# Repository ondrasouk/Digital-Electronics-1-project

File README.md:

# Týmový projekt do předmětu BPC-DE1 
# Název projektu: Konzole pro rotoped 

### Členové týmu

1. [Smejkal Marek](https://github.com/xsmejk30/Digital-electronics-1)
2. [Socha Jakub](https://github.com/xsocha00/Digital-electronics-1)
3. [Soukeník Ondřej](https://github.com/ondrasouk/Digital-electronics-1)
4. [Stupka Tomáš](https://github.com/ondrasouk/Digital-electronics-1)
5. [Šomšák Martin ](https://github.com/MartinSomsak00/DE1)

[Link to GitHub project folder](https://github.com/ondrasouk/Digital-Electronics-1-project)

## Úvod

Úkolem tohoto projektu bylo vytvořit konzoli pro měření otáček rotopedu. Toto měření následně vede na rozšíření jako napříkad měření rychlosti, ujeté vzdálenosti, průměrné rychlosti atd. 

V našem případě jsme se rozhodli pro snímání otáček použít čidlo [44E](https://dratek.cz/arduino/7735-halluv-senzor-44e.html?gclid=CjwKCAjwj6SEBhAOEiwAvFRuKIS_8uQ_ZEzr9x-yYRR3fPEQ0RS04KZdMaqaGm8xElUVrgnHnGZ3SxoCdZ4QAvD_BwE), který obsahuje halovu sondu. Napájecí napětí čidla je 4,5-24V Výstupem čidla je buď logická 0 nebo 1. Pokud tento sensor umístíme na pevný bod v blízkoti otáčenícího kola, je nutné přidat na otáčejí se kole magnetický puk. Následně při otáčení kola snímač vygeneruje signál pomocí kterého můžeme určit požadované veličiny.

Pro následní zobrazení měřené veličiny byl využit 4x7 segmentový displej a tři ledky pro indikaci zobrazovaného výstupu (zapnuto/vypnuto, přepínání zobrazení, reset systému).

## Popis zapojení 
Zapojení a PCB jsou navrženy v programu Eagle. 
V zapojení jsou použity 7 segmentové displeje se společnou anodou. Stejné segmenty jednotlivých digitů jsou pospojovány. Pmod JC slouží k přepínání napájení mezi jednotlivými digity. K Pmod JB jsou připojeny jednotlivé skupiny segmentů a k Pmod JA jsou připojeny LED a hallův senzor. Výhodnější by bylo pouřít jednou součástku obsahující 4 digity (stejně jako na desce Nexys A7), ale Eagle takovou součástku neobsahuje.
PADy 1, 2 a 3 slouží k připojení hallova senzoru. PAD1 je určen k připojení +5V protože použitý hallův senzor pracuje od 4,5V, ale na Pmod porty mají 3,3V. 

| **PCB** | **Pmod JA** | **Port** |
| :-: | :-: | :-: |
| AN0 | 4 | D12 |
| AN1 | 3 | A11 | 
| AN2 | 2 | B11 | 
| AN3 | 1 | G13 | 

| **PCB** | **Pmod JB** | **Port** |
| :-: | :-: | :-: |
| a | 1 | E15 |
| b | 2 | E16 | 
| c | 3 | D15 | 
| d | 4 | C15 | 
| e | 7 | J17 | 
| f | 8 | J18 | 
| g | 9 | K15 | 
| P | 10 | J15 |
| GND | 5 |  |
| 3,3V | 6 |  |

| **PCB** | **Pmod JC** | **Port** |
| :-: | :-: | :-: |
| LED1 | 1 | U12 |
| LED2 | 2 | V12 | 
| LED3 | 3 | V10 | 
| LED4 | 4 | V11 | 
| LED5 | 7 | T13 | 
| hall sensor | 8 | U13 | 

## Programová část
### Popis řešení měření času
Čidlo vždy vygeneruje klesající hranu, když kolem něj projede magnet umístěný na kole setrvačníku. V top modulu vstup invertujeme, pro snažší pochopení. Tento signál značí jednu otáčku setrvačníku, který simuluje setrvačnost jízdního kola a člověka na něm. Interval mezi klesajícími hranami je tedy doba za kterou virtuální kolo urazí jednu otočku kola. Podle vzorečku v=s/t můžeme vypočítat rychlost, kde s je virtuální vzdálenost jedné otočky setrvačníku (je tedy konstantní) a t je čas mezi signálem ze senzoru.

K měření času se dá použít hodinový zdroj z FPGA který má 100&nbsp;MHz. Rozlišovací schopnost 10&nbsp;ns je pro toto použití moc přesná a plítvali bychom zbytečně prostředky na např. 32 bitovém čitači, když můžeme použít 16 bitový. Tedy aby pro čas kolem 250&nbsp;us se musí prodloužit interval mezi náběžnými hranami. Pro tento účel byla použita dělička časových hodin v podobě modulu clock_enable, který byl využit z cvičení v předmětu DE1. Poté něčím musíme počítat jednotlivé pulzy. Zde byl využit naprogramovaný obousměrný čítač  ze cvičení, který pro tento účel zjednodušíme a uděláme z něj jen jednoduchý čítač nahoru. Nasčítaný počet pulzů tedy odpovídá času, který trvala jedna otočka setrvačníku. Pro vyšší přesnost se při každé otočce vyresetuje i modul clock_enable.
#### Náhled do bloku s instancemi `clock_enable` a `cnt_up` a procesu `p_etime` (elapsed time)
```vhdl
    --------------------------------------------------------------------
    -- Instance (copy) of clock_enable entity
    clk_en1 : entity work.clock_enable
        generic map(
            g_MAX => g_TIME_UNIT_LENGHT
        )
        port map(
            clk => clk,
            reset => s_rst_t,
            ce_o => s_en
        );

    --------------------------------------------------------------------
    -- Instance (copy) of cnt_up entity
    bin_cnt0 : entity work.cnt_up
        generic map(
            g_CNT_WIDTH => 16
        )
        port map(
            clk => clk,
            reset => s_rst_t,
            en_i => s_en,
            cnt_o => s_etime
        );

    --------------------------------------------------------------------
    -- p_etime:
    -- Measure elapsed time using clock divider and counter.
    --------------------------------------------------------------------
    p_etime : process(clk,hall_sensor_i,reset)
    begin
        if reset = '1' then
            s_rst_t <= '1';
            s_etime_local <= (others => '0');
            s_distance_local <= (others => '0');
            s_skip <= '1';
        elsif ((s_rst_t = '1') and (s_etime = x"0000")) then
            s_rst_t <= '0'; -- on the next clock take down the reset for timer
        elsif (unsigned(s_etime) > g_ETIME_ZERO) then
            s_etime_local <= (others => '0');
            s_skip <= '1';
        end if;
        if rising_edge(hall_sensor_i) then
            if (s_skip = '1') and (reset = '0') then
                s_rst_t <= '1';
                s_skip <= '0';
            elsif reset = '0' then
                s_etime_local <= unsigned(s_etime);
                s_distance_local <= s_distance_local + 1;
                s_rst_t <= '1'; -- reset the timer and clock divider
            end if;
        end if;
    end process p_etime;
```
#### Popis kódu
Proces p_etime má za úkol měřit čas, počítat vstupní hodnoty, přiřazovat naměřený čas do signálu `s_etime_local` a posílat signál `s_rst_t` a tím resetovat `clk_en1` a `bin_cnt0`. Reset proběhne vždy když příjde náběžná hrana z hallova senzoru. Také se musí kontrolovat, jestli už neuplynula moc dlouhá doba od posledního vstupu a v případě potřeby vynulovat čas v signálu `s_etime`. V tomto případě je potřeba přeskočit další měření, kdeby mohla kvůli jedoucímu čítači přetéct maximální hodnota času (0.1*2^16&nbsp;ms&nbsp;=&nbsp;6.5536&nbsp;s) a mohlo by to odečíst špatnou hodnotu. Pro tento účel je zde signál `s_skip`, který zaručí, že při další náběžné hraně se aktuální hodnota nebude měřit a jen proběhne reset čítače a děliče. Lokální reset `s_rst_t` trvá do dalšího clocku a dokud není vyresetovaný čitač. Při globálním resetu se vyresetuje vše a nastaví se `s_skip`, aby to další náběžnou hranu nepočítalo. 

### Počítání rychlosti, vzdálenosti a energie
Rychlost se počítá pomocí vzorečku v=s/t. Tedy v\[*dm/s*\]&nbsp;=&nbsp;`g_WHEEL_CIRCUMFERENCE`\[*cm*\]/`s_etime`\[*ms/10*\]. Vzdálenost se počítá podle otočení setrvačníku násobeného obvodem virtuálního kola (`g_WHEEL_CIRCUMFERENCE`).

Energie mezi otočením se dá rozdělit na rozdíl kinetických energií mezi otečením a aktuálnímu odporu (zátěže) potřebné pro jedno otočení. Kinetická energie se spočítá jako Eₖ&nbsp;=&nbsp;1/2&nbsp;J&nbsp;ω². Práce je součet vykonané energie, tedy pokud budeme počítat jednotlivé díly jak roste, tak dojdeme k celkové energii. Design programu je tímto připraven například na měření okamžitého výkonu.

Pro zátěž počítáme s teoretickou, která bude sestávat jen z práce potřebné pro jednu otočku tedy čím vyšší úhlová rychlost, tím vyšší odpor. Výpočet Wₒ&nbsp;=&nbsp;2π F<sub>b</sub> .
V Programu se jedná o `g_RESISTLOAD` a o `g_INERTIA_MOMENT`, kde `g_INERTIA_MOMENT` musí být vynásoben 10000π, aby odpovídal jednotkám SI.

#### Náhled na kód procesu `p_calc` a přiřazení dat výstupním signálům
```vhdl
    --------------------------------------------------------------------
    -- p_calc:
    -- Calculate actual speed (average of last four speeds).
    -- Also monitor maximal speed, calories in total.
    --------------------------------------------------------------------
    p_calc : process(hall_sensor_i,reset,s_etime_local)
    begin
        if falling_edge(reset) then
            s_speed_local <= (others => '0');
            s_speed1_local <= (others => '0');
            s_speed2_local <= (others => '0');
            s_speed3_local <= (others => '0');
            s_avg_speed_local <= (others => '0');
            s_max_speed_local <= (others => '0');
            s_inertia_local <= (others => '0');
            s_inertia1_local <= (others => '0');
            s_work_local <= (others => '0');
        end if;
        if (s_etime_local = x"0000") and (reset = '0') then --flywheel is stopped
            s_speed_local <= (others => '0');
            s_speed1_local <= (others => '0');
            s_speed2_local <= (others => '0');
            s_speed3_local <= (others => '0');
            s_avg_speed_local <= (others => '0');
            s_inertia_local <= (others => '0');
        end if;
        if rising_edge(hall_sensor_i) and not(s_etime_local = x"0000") then
            if reset = '0' then
                s_speed3_local <= s_speed2_local;
                s_speed2_local <= s_speed1_local;
                s_speed1_local <= s_speed_local;
                s_speed_local <= (g_WHEEL_CIRCUMFERENCE*10000/resize(s_etime_local, 22)); -- m*1e-6/s*1e-4=cm/s
                s_avg_speed_local <= resize(resize(s_speed_local+s_speed1_local+s_speed2_local+s_speed3_local, 24)/4, 22);
                if (s_max_speed_local < s_avg_speed_local) then
                    s_max_speed_local <= s_avg_speed_local;
                end if;
                s_inertia1_local <= s_inertia_local;
                s_inertia_local <= resize(g_INERTIA_MOMENT/((s_etime_local * s_etime_local)/5000), 16);
                s_work_local <= s_work_local + s_inertia_local - s_inertia1_local + g_RESISTLOAD; -- in Joules
            end if;
        end if;
    end process p_calc;
    
    speed_o <= std_logic_vector(resize(resize(s_avg_speed_local*36, 26)/10, 22));
    max_speed_o <= std_logic_vector(resize(resize(s_max_speed_local*36, 26)/10, 22));
    distance_o <= std_logic_vector(resize(resize(s_distance_local * g_WHEEL_CIRCUMFERENCE, 30) / 100, 22));
    calories_o <= std_logic_vector(resize(resize(s_work_local*1000, 26)/4184, 22)); -- 1cal = 4.184 Joules
```
#### Popis kódu
Proces `p_calc` v normálním chodu (není nastaven `reset` ani `s_etime_local` není vynulovaný) nejprve přesune všechny důležité hodnoty z minulých běhů a uvolní tak místo pro aktuální hodnotu rychlosti `s_speed_local`, poté se vypočítá průměr čtyř předchozích rychlostí `s_avg_speed_local` a vyzkouší se, jestli to není nová nejvyšší rychlost `s_max_speed_local`. Poté se uloží minulá kinetická energie a vypočítá se aktuální. `s_work_local` je dosavadní práce, rozdíl kinetických energií setrvačníku a přičtení `g_RESISTLOAD`, protože setrvačník udělal jedno otočení. Signál `reset` vynuluje všechny lokální proměnné používané tímto procesem. V případě že reset není nastaven, ale čas mezi pulsy je na nule, tedymoc dlouho se čekalo na další pulz z hallova senzoru se vynulují rychlosti a kinetická energie, tedy setrvačník se virtuálně zastaví. Tento stav se musí ošetřovat zvlášť, protože dělit nulou nemůžeme a nejvyšší možná hodnota `s_etime` se neblíží nekonečnu, hlavně 2500000 > 2^16, tedy nikdy nevýjde nula i s tím, že dělení ve VHDL zaokrouhluje vždy dolů.

Přiřazování hodnot je jen převod na jednotky vhodnější k použití v displeji. Např. z *cm/s* převádíme do desítek metrů za hodinu (násobíme 3.6). Vzdálenost je násobení počtu otočení setrvačníku a obvodu virtuálního kola, kde výsledek je v metrech. Jouly převádíme na kalorie, které jsou větší a častěji se používají na cvičících strojích, kde jsou v kilokaloriích.

#### Simulace 
V simulaci je simulován postupné zrychlení na 10 m/s (36 km/h) a poté prudké zastavení, kde se testuje vynulování po dlouhé době bez hrany. Mohlo by se toho testovat více např. po každém pulzu ze senzoru rychlost nebo tak, ale myslím, že vizuální kontrola výsledků je jednodušší a rychlejší. Kontroluje se tedy jen rychlost na začátku po jednom pulzu (test jestli funguje správně `s_skip`), vzdálenost po ujetých deseti metrech a rychlost při konstantní rychlosti. Dělička hodinového signálu je nastavena na tisícinu normální hodnoty, aby simulace netrvala extrémně dlouho (místo 20 s je to 20 ms).

Na Obrázku ze simulace můžeme vidět rozběhnutí. Odpor a moment hybnosti jsem počítal jako rychlost pohybujícího se dospělého a kola - 80 kg a odpor jsem počítal, aby při 36 km/h byl potřebný výkon dodávaný na šlapátka 80 W. 

Podle kinetické energie hmotného bodu Eₖ&nbsp;=&nbsp;1/2&nbsp;m&nbsp;v² (v = o/T; o - obvod kola) si můžeme odvodit jaké parametry musí mít moment setrvačnosti J. Poté můžeme nastavit odpor na nulu a pozorovat, že nám vyjde přesně vypočítaný výkon na konci rozběhu. Délka rozběhu byla volená daleko kratší než by byla v reálných podmínkách, ale účel to splní. Kvůli zaokrouhlování při dělení vždy dolů bude chyba mířit také dolů a výsledek bude o trochu menší než očekávání.

Na druhém obrázku vidíme správnou funkci vynulování rychlostí.
### Převádění vypočtených hodnot do formátu pro driver sedmi segmentového displeje
Kód ve display_control by se dal rozdělit na tři části:
1) celkový čas
2) přepínání obrazovek a reset
3) konverze vstupních signálů do formátu zpracovatelného driverem na sedmi segmentový displej

Se počítá pomocí instance `clk_en2` a `p_total_time`, každou sekundu se přičte jednička do `s_total_time`, při `reset` se čas vynuluje.

Přepínání obrazovek obsluhuje instance `clk_en3` a `bin_cnt1` a proces `p_display_selection`, který při stisknutí tlačítka `button_i` přepne na další obrazovku, pokud je tlačítko stisknuto jen krátce a pokud dlouze více než osm sekund, tak nastaví signál `reset` na jedničku a po proběhnutí resetu ho zase nastaví na nulu. Doba stisku se počítá pomocí `clk_en3` a `bin_cnt1`. Přepnutí obrazovky nastane až se sestupnou hranou.

V procesu `p_display_control` se pomocí operací děleno a modulo rozdělují jednotlivé dekadické hodnoty a přiřazují se `dataX_o`, kde je uložená vždy jedna číslice pro displej. `data0_o` je číslice na sedmisegmentu nejvíce v pravo `data3_o` je číslice nejvíce vlevo.

#### Náhled na kód v architecture display_control.vhdl
```vhdl
    --------------------------------------------------------------------
    -- Instance (copy) of clock_enable entity
    clk_en2 : entity work.clock_enable
        generic map(
            g_MAX => g_clk_div_sec
        )
        port map(
            clk => clk,
            reset => s_reset,
            ce_o => s_en_t
        );
    --------------------------------------------------------------------
    -- Instance (copy) of clock_enable entity
    clk_en3 : entity work.clock_enable
        generic map(
            g_MAX => g_time_for_reset
        )
        port map(
            clk => clk,
            reset => s_rst_r_local,
            ce_o => s_en_r
        );

    --------------------------------------------------------------------
    -- Instance (copy) of cnt_up entity
    bin_cnt1 : entity work.cnt_up
        generic map(
            g_CNT_WIDTH => 19
        )
        port map(
            clk => clk,
            reset => s_reset,
            en_i => s_en_t,
            unsigned(cnt_o) => s_total_time
        );

    --------------------------------------------------------------------
    -- p_display_selection:
    -- Counter reacting for falling edge of button and when long press
    -- (8s) s_reset sets on and then off.
    --------------------------------------------------------------------
    p_display_selection : process(clk, button_i, s_en_r)
    begin
        if (button_i = '1') and (s_button_last_local = '0') then
            s_rst_r_local <= '0';
            s_button_last_local <= '1';
        elsif (button_i = '0') and (s_button_last_local = '1') then
            s_sel_display_local <= s_sel_display_local + 1;
            if (s_sel_display_local > x"3") then
                s_sel_display_local <= x"0";
            end if;
            s_rst_r_local <= '1';
            s_rst_t_local <= "00";
            s_button_last_local <= '0';
        end if;
        if rising_edge(s_en_r) then
            if s_rst_t_local = "11" then
                s_rst_t_local <= (others => '0');
                s_rst_r_local <= '1';
                s_sel_display_local <= x"4";
                s_reset <= '1';
            else
                s_rst_t_local <= s_rst_t_local + 1;
            end if;
        end if;
        if (s_reset = '1') and rising_edge(clk) and (s_total_time = 0) then
            s_reset <= '0';
            s_rst_t_local <= (others => '0');
        end if;
    end process p_display_selection;

    --------------------------------------------------------------------
    -- p_display_control:
    -- Converts input number to format that is compatible with 
    -- driver_7seg_4digits and displays only one number.
    -- note:
    --   The omitted numbers is rounded down so 155.79 km -> 155.7 km.
    --------------------------------------------------------------------
    p_display_control : process(clk)
    begin
        case s_sel_display_local is
            when x"0" => -- speed
                s_temp_local <= unsigned(speed_i);
                leds_o <= b"10000";
                if ((s_temp_local / 10000) < 1) then -- format DD.DD
                    dp_o <= b"1011";
                    data3_o <= std_logic_vector(resize(s_temp_local / 1000, 4));
                    data2_o <= std_logic_vector(resize((s_temp_local mod 1000) / 100, 4));
                    data1_o <= std_logic_vector(resize((s_temp_local mod 100) / 10, 4));
                    data0_o <= std_logic_vector(resize(s_temp_local mod 10, 4));
                elsif ((s_temp_local / 100000) < 1) then -- format DDD.D
                    dp_o <= b"1101";
                    data3_o <= std_logic_vector(resize(s_temp_local / 10000, 4));
                    data2_o <= std_logic_vector(resize((s_temp_local mod 10000) / 1000, 4));
                    data1_o <= std_logic_vector(resize((s_temp_local mod 1000) / 100, 4));
                    data0_o <= std_logic_vector(resize((s_temp_local mod 100) / 10, 4));
                elsif ((s_temp_local / 1000000) < 1) then -- format DDDD
                    dp_o <= b"1111";
                    data3_o <= std_logic_vector(resize(s_temp_local / 100000, 4));
                    data2_o <= std_logic_vector(resize((s_temp_local mod 100000) / 10000, 4));
                    data1_o <= std_logic_vector(resize((s_temp_local mod 10000) / 1000, 4));
                    data0_o <= std_logic_vector(resize((s_temp_local mod 1000) / 100, 4));
                else -- for higher numbers display only 9999
                    dp_o <= b"1111";
                    data3_o <= x"9";
                    data2_o <= x"9";
                    data1_o <= x"9";
                    data0_o <= x"9";
                end if;
            when x"1" => -- distance
                s_temp_local <= unsigned(distance_i);
                leds_o <= b"01000";
                if ((s_temp_local / 10000) < 1) then -- format D.DDD
                    dp_o <= b"0111";
                    data3_o <= std_logic_vector(resize(s_temp_local / 1000, 4));
                    data2_o <= std_logic_vector(resize((s_temp_local mod 1000) / 100, 4));
                    data1_o <= std_logic_vector(resize((s_temp_local mod 100) / 10, 4));
                    data0_o <= std_logic_vector(resize(s_temp_local mod 10, 4));
                elsif ((s_temp_local / 100000) < 1) then -- format DD.DD
                    dp_o <= b"1011";
                    data3_o <= std_logic_vector(resize(s_temp_local / 10000, 4));
                    data2_o <= std_logic_vector(resize((s_temp_local mod 10000) / 1000, 4));
                    data1_o <= std_logic_vector(resize((s_temp_local mod 1000) / 100, 4));
                    data0_o <= std_logic_vector(resize((s_temp_local mod 100) / 10, 4));
                elsif ((s_temp_local / 1000000) < 1) then -- format DDD.D
                    dp_o <= b"1101";
                    data3_o <= std_logic_vector(resize(s_temp_local / 100000, 4));
                    data2_o <= std_logic_vector(resize((s_temp_local mod 100000) / 10000, 4));
                    data1_o <= std_logic_vector(resize((s_temp_local mod 10000) / 1000, 4));
                    data0_o <= std_logic_vector(resize((s_temp_local mod 1000) / 100, 4));
                elsif ((s_temp_local / 10000000) < 1) then -- format DDDD
                    dp_o <= b"1111";
                    data3_o <= std_logic_vector(resize(s_temp_local / 1000000, 4));
                    data2_o <= std_logic_vector(resize((s_temp_local mod 1000000) / 100000, 4));
                    data1_o <= std_logic_vector(resize((s_temp_local mod 100000) / 10000, 4));
                    data0_o <= std_logic_vector(resize((s_temp_local mod 10000) / 1000, 4));
                end if;
            when x"2" => -- kcalories
                s_temp_local <= unsigned(calories_i);
                leds_o <= b"00100";
                if ((s_temp_local / 10000) < 1) then -- format D.DDD
                    dp_o <= b"0111";
                    data3_o <= std_logic_vector(resize(s_temp_local / 1000, 4));
                    data2_o <= std_logic_vector(resize((s_temp_local mod 1000) / 100, 4));
                    data1_o <= std_logic_vector(resize((s_temp_local mod 100) / 10, 4));
                    data0_o <= std_logic_vector(resize(s_temp_local mod 10, 4));
                elsif ((s_temp_local / 100000) < 1) then -- format DD.DD
                    dp_o <= b"1011";
                    data3_o <= std_logic_vector(resize(s_temp_local / 10000, 4));
                    data2_o <= std_logic_vector(resize((s_temp_local mod 10000) / 1000, 4));
                    data1_o <= std_logic_vector(resize((s_temp_local mod 1000) / 100, 4));
                    data0_o <= std_logic_vector(resize((s_temp_local mod 100) / 10, 4));
                elsif ((s_temp_local / 1000000) < 1) then -- format DDD.D
                    dp_o <= b"1101";
                    data3_o <= std_logic_vector(resize(s_temp_local / 100000, 4));
                    data2_o <= std_logic_vector(resize((s_temp_local mod 100000) / 10000, 4));
                    data1_o <= std_logic_vector(resize((s_temp_local mod 10000) / 1000, 4));
                    data0_o <= std_logic_vector(resize((s_temp_local mod 1000) / 100, 4));
                elsif ((s_temp_local / 10000000) < 1) then -- format DDDD
                    dp_o <= b"1111";
                    data3_o <= std_logic_vector(resize(s_temp_local / 1000000, 4));
                    data2_o <= std_logic_vector(resize((s_temp_local mod 1000000) / 100000, 4));
                    data1_o <= std_logic_vector(resize((s_temp_local mod 100000) / 10000, 4));
                    data0_o <= std_logic_vector(resize((s_temp_local mod 10000) / 1000, 4));
                end if;
            when x"3" => -- total time
                leds_o <= b"00010";
                if (s_total_time < 3600) then -- MM.SS
                    dp_o <= b"1011";
                    data3_o <= std_logic_vector(resize((s_total_time / 60) / 10, 4));
                    data2_o <= std_logic_vector(resize((s_total_time / 60) mod 10, 4));
                    data1_o <= std_logic_vector(resize((s_total_time mod 60) / 10, 4));
                    data0_o <= std_logic_vector(resize((s_total_time mod 60) mod 10, 4));
                else -- HH.MM
                    dp_o <= b"1011";
                    data3_o <= std_logic_vector(resize((s_total_time / 3600) / 10, 4));
                    data2_o <= std_logic_vector(resize((s_total_time / 3600) mod 10, 4));
                    data1_o <= std_logic_vector(resize(((s_total_time mod 3600) / 60) / 10, 4));
                    data0_o <= std_logic_vector(resize(((s_total_time mod 3600) / 60) mod 10, 4));
                end if;
            when x"4" => -- maximal speed
                s_temp_local <= unsigned(max_speed_i);
                leds_o <= b"00001";
                if ((s_temp_local / 10000) < 1) then -- format DD.DD
                    dp_o <= b"1011";
                    data3_o <= std_logic_vector(resize(s_temp_local / 1000, 4));
                    data2_o <= std_logic_vector(resize((s_temp_local mod 1000) / 100, 4));
                    data1_o <= std_logic_vector(resize((s_temp_local mod 100) / 10, 4));
                    data0_o <= std_logic_vector(resize(s_temp_local mod 10, 4));
                elsif ((s_temp_local / 100000) < 1) then -- format DDD.D
                    dp_o <= b"1101";
                    data3_o <= std_logic_vector(resize(s_temp_local / 10000, 4));
                    data2_o <= std_logic_vector(resize((s_temp_local mod 10000) / 1000, 4));
                    data1_o <= std_logic_vector(resize((s_temp_local mod 1000) / 100, 4));
                    data0_o <= std_logic_vector(resize((s_temp_local mod 100) / 10, 4));
                elsif ((s_temp_local / 1000000) < 1) then -- format DDDD
                    dp_o <= b"1111";
                    data3_o <= std_logic_vector(resize(s_temp_local / 100000, 4));
                    data2_o <= std_logic_vector(resize((s_temp_local mod 100000) / 10000, 4));
                    data1_o <= std_logic_vector(resize((s_temp_local mod 10000) / 1000, 4));
                    data0_o <= std_logic_vector(resize((s_temp_local mod 1000) / 100, 4));
                else -- for higher numbers display only 9999
                    dp_o <= b"1111";
                    data3_o <= x"9";
                    data2_o <= x"9";
                    data1_o <= x"9";
                    data0_o <= x"9";
                end if;
            when others => -- there are no other states.
        end case;
    end process p_display_control;

    reset <= s_reset;
```

#### Simulace 
Simulace probíhá tím, že se testuje zobrazení různě velkých čísel a potom se pomocí assertů kontroluje výstupní hodnota. Postupně se zkouší také různé režimy zobrazení a na závěr se testuje dlouhé podržení pro nastavení `reset` a potom jeho vypnutí.

Poznámka: Simulace pracuje v mnohem kratším časovém intervalu a tedy výstupní signály nejsou naprosto čisté, ale normálně se neproklikává displej takovou rychlostí, přebliknutí hodnot z minulého displeje není kritické.

Simulace kompletního projektu je zbytečná, protože výstupní hodnoty pro sedmisegmentový display jsou špatně čitelné a vyzkoušení veškeré funkcionality dohromady velmi náročné. 

### Blokové schéma top.vhdl

### kód top modulu
```vhdl
entity top is
    Port (
        CLK100MHZ   : in STD_LOGIC;
        btn0        : in STD_LOGIC; -- right BTN0 button
        AN0         : out STD_LOGIC; -- AN0
        AN1         : out STD_LOGIC; -- AN1
        AN2         : out STD_LOGIC; -- AN2
        AN3         : out STD_LOGIC; -- AN3
        A           : out STD_LOGIC; -- A
        B           : out STD_LOGIC; -- B
        C           : out STD_LOGIC; -- C
        D           : out STD_LOGIC; -- D
        E           : out STD_LOGIC; -- E
        F           : out STD_LOGIC; -- F
        G           : out STD_LOGIC; -- G
        P           : out STD_LOGIC; -- P (DP)
        LED1        : out STD_LOGIC; -- LED1
        LED2        : out STD_LOGIC; -- LED2
        LED3        : out STD_LOGIC; -- LED3
        LED4        : out STD_LOGIC; -- LED4
        LED5        : out STD_LOGIC; -- LED5
        HALL        : in STD_LOGIC  -- Hall sensor
    );
end top;

architecture Behavioral of top is
    -- outternal reset
    signal s_reset      : std_logic;
    
    signal s_speed      : std_logic_vector(22 - 1 downto 0);
    signal s_distance   : std_logic_vector(22 - 1 downto 0);
    signal s_calories   : std_logic_vector(22 - 1 downto 0);
    signal s_max_speed  : std_logic_vector(22 - 1 downto 0);
    
    signal s_dp         : std_logic_vector(4 - 1 downto 0);
    signal s_data0      : std_logic_vector(4 - 1 downto 0);
    signal s_data1      : std_logic_vector(4 - 1 downto 0);
    signal s_data2      : std_logic_vector(4 - 1 downto 0);
    signal s_data3      : std_logic_vector(4 - 1 downto 0);

begin

    --------------------------------------------------------------------
    -- outstance (copy) of speedometer entity
    speedometer : entity work.speedometer
        port map(
            clk             => CLK100MHZ,
            reset           => s_reset,
            hall_sensor_i   => HALL,
            speed_o         => s_speed,
            distance_o      => s_distance,
            calories_o      => s_calories,
            max_speed_o     => s_max_speed
        );
        
    --------------------------------------------------------------------
    -- outstance (copy) of display_control entity
    display_control : entity work.display_control
        port map(
            clk         => CLK100MHZ,
            speed_i     => s_speed,
            distance_i  => s_distance,
            calories_i  => s_calories,
            max_speed_i => s_max_speed,
            button_i    => btn0,
            reset       => s_reset,
            leds_o(0)   => LED1,
            leds_o(1)   => LED2,
            leds_o(2)   => LED3,
            leds_o(3)   => LED4,
            leds_o(4)   => LED5
        );

    --------------------------------------------------------------------
    -- outstance (copy) of driver_7seg_4digits entity
    driver_seg_4 : entity work.driver_7seg_4digits
        port map(
            clk         => CLK100MHZ,
            reset       => s_reset,
            data0_i     => s_data0,
            data1_i     => s_data1,
            data2_i     => s_data2,
            data3_i     => s_data3,
            dp_i        => s_dp,
            seg_o(6)    => A,
            seg_o(5)    => B,
            seg_o(4)    => C,
            seg_o(3)    => D,
            seg_o(2)    => E,
            seg_o(1)    => F,
            seg_o(0)    => G,
            dp_o        => P,
            dig_o(0)    => AN0,
            dig_o(1)    => AN1,
            dig_o(2)    => AN2,
            dig_o(3)    => AN3
        );

end Behavioral;
```
## Video

[Link na video prezentace](https://www.youtube.com/watch?v=75vinimI-LY&feature=youtu.be)

## Reference

   1. [https://store.digilentinc.com/arty-a7-artix-7-fpga-development-board/](https://store.digilentinc.com/arty-a7-artix-7-fpga-development-board/)
   2. [https://reference.digilentinc.com/reference/programmable-logic/arty-a7/reference-manual](https://reference.digilentinc.com/reference/programmable-logic/arty-a7/reference-manual)
   3. [arty_a7_sch.pdf](Docs/arty_a7_sch.pdf)
   4. [44E datasheet](https://dratek.cz/docs/produkty/0/908/a3144eu.pdf)

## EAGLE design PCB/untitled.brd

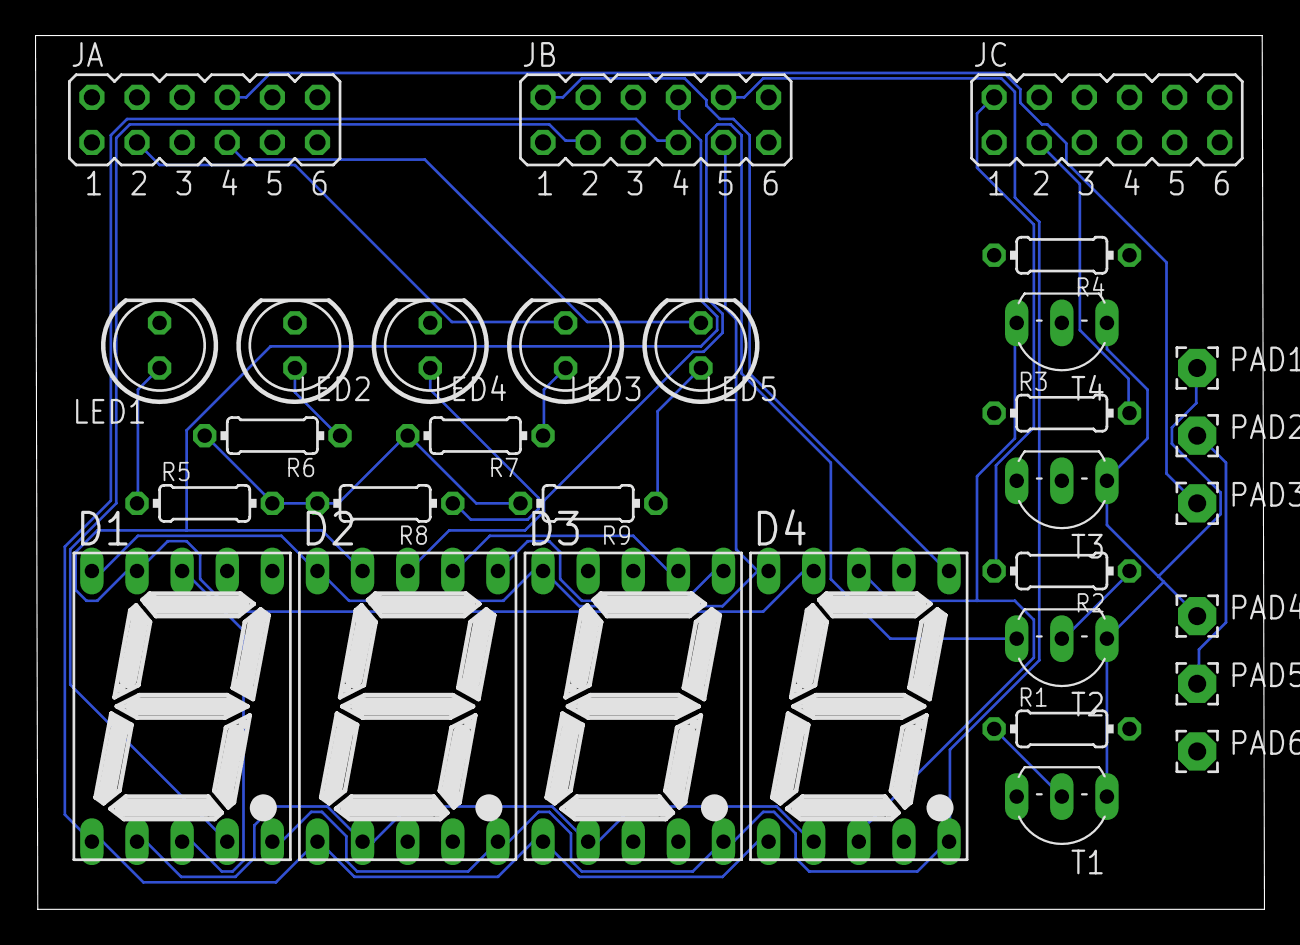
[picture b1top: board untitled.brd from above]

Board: 4 copper layers, 69.2 x 49.2 mm, 31 parts (0 on the bottom side), 34 nets.

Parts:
D1, D2, D3, D4: 7SEG-13
JA: JP6Q
JB: JP6Q
JC: JP6Q
LED1, LED2, LED3, LED4, LED5: LED5MM
PAD1: +5V hall sensor; 2,15/1,0
PAD2: GND hall sensor; 2,15/1,0
PAD3: hall sensor digital out; 2,15/1,0
PAD4: +5V; 2,15/1,0
PAD5: GND; 2,15/1,0
PAD6: +3,3V; 2,15/1,0
R1, R2, R3, R4, R5, R6, R7, R8, R9: 0204/7
T1, T2, T3, T4: TO92-EBC

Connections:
unnamed: D1.7, D2.7, D3.7, D4.7, JB.1
unnamed: D1.6, D2.6, D3.6, D4.6, JB.2
unnamed: D1.2, D2.2, D3.2, D4.2, JB.4
unnamed: D1.4, D2.4, D3.4, D4.4, JB.3
unnamed: D1.1, D2.1, D3.1, D4.1, JB.7
unnamed: D1.9, D2.9, D3.9, D4.9, JB.8
unnamed: D1.10, D2.10, D3.10, D4.10, JB.9
unnamed: D1.5, D2.5, D3.5, D4.5, JB.10
unnamed: D1.3, D1.8, T1.C
unnamed: D2.3, D2.8, T2.C
unnamed: D3.3, D3.8, T3.C
unnamed: D4.3, D4.8, T4.C
unnamed: PAD1.1, PAD4.1, R5.2, R6.2, R7.2, R8.2, R9.2, T1.E, T2.E, T3.E, T4.E
unnamed: R1.1, T1.B
unnamed: R2.1, T2.B
unnamed: R3.1, T3.B
unnamed: R4.1, T4.B
unnamed: LED1.A, R5.1
unnamed: LED2.A, R6.1
unnamed: LED3.A, R7.1
unnamed: LED4.A, R8.1
unnamed: LED5.A, R9.1
unnamed: JC.1, R1.2
unnamed: JC.2, R2.2
unnamed: JC.3, R3.2
unnamed: JC.4, R4.2
unnamed: JA.1, LED1.K
unnamed: JA.2, LED2.K
unnamed: JA.3, LED3.K
unnamed: JA.4, LED4.K
unnamed: JA.7, LED5.K
unnamed: JA.8, PAD3.1
unnamed: JB.5, PAD2.1, PAD5.1
unnamed: JB.6, PAD6.1

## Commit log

2021-04-16 added scheme for board and updated README.md
2021-04-21 Initial code drop of vivado project.
2021-04-21 speedometer fixes
2021-04-21 speedometer - make more standart output for display control
2021-04-22 Added display controller. Now only testbenches and top level.
2021-04-28 Add basic description for VHDL code in speedometer.vhdl
2021-04-30 Fix arithmetical operations and uninitialized values speedometer.vhdl
2021-04-30 exclude simulation cache files wdb files is large binary files containing latest simulation output.
2021-04-30 small fixes
2021-04-30 testbench for speedometer Not complete testbench, without data validation.
2021-04-30 Clean unsused signals in testbench. No need for importing internal signals, we can change scope on left from waveforms.
2021-05-01 Initial workbench for display control.
2021-05-01 Make entity outputs and inputs compilant with naming style rules.
2021-05-01 work in top level
2021-05-01 Finished display_control testbench and added image from it
2021-05-01 Completed the testbench for speedometer.
2021-05-03 Added description of elapsed time measuring.
2021-05-03 added code description for p_etime
2021-05-03 Added description of p_calc
2021-05-03 Reworked calculation of calories, now more precise and accurate
2021-05-03 Added description of p_calc code
2021-05-03 Added text about assigning values in speedometer
2021-05-03 Added to README simulations of speedometer.vhdl
2021-05-03 fixed images
2021-05-03 Finished code description
2021-05-04 fix ports
2021-05-04 Make project synthesizable
2021-05-04 Update code listings
2021-05-04 Make PDF version of README
2021-05-04 last fixes
2021-05-04 update README files
2021-05-06 Fix Bitstream generation In placer, there were two problems: 1) in top I was pointing at package ports and not ports named in constrains file 2) I was using clocked operations on port that doesn't su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
